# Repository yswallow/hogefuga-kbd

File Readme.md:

### hogefuga keyboard

#### PCB size

```
Plate:  76.2mm x 95.25mm, 1.2mm thick
PCB:    97.7mm x 95.25mm
bottom: 97.7mm x 95.25mm
```

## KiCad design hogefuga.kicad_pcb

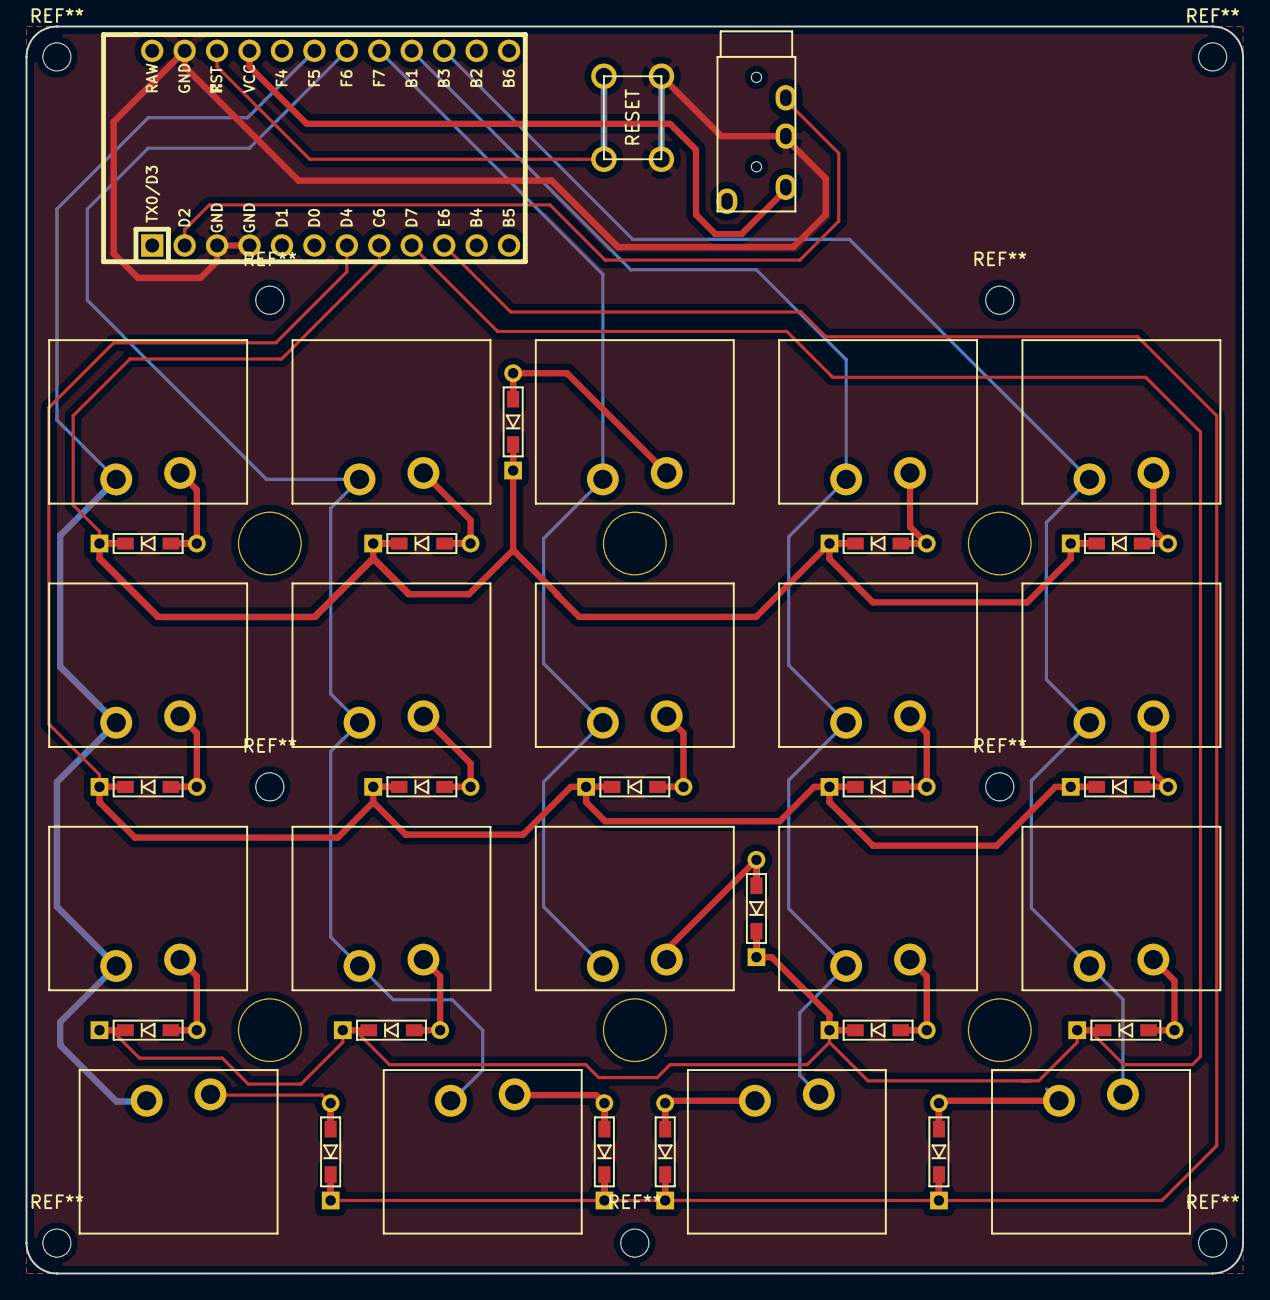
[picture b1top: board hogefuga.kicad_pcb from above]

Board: 2 copper layers, 95.3 x 97.6 mm, 47 parts (0 on the bottom side), 32 nets.

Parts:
D1, D2, D3, D4, D5, D6, D7, D8, D9, D10, D11, D12, D13, D14, D15, D16, D17, D18, D19: D; D3_TH_SMD
J1: MJ-4PP-9; Keebio-PJ-320A
Ref**: Val**; HOLE
Ref**#2, Ref**#3, Ref**#4, Ref**#5, Ref**#6: Val**; HOLE
SW1, SW2, SW3, SW4, SW5, SW6, SW7, SW8, SW9, SW10, SW11, SW12, SW13, SW14, SW15, SW16, SW17, SW18, SW19: SW_PUSH; ALPS_SKCM
SW20: SW_PUSH; ResetSW_4P
U1: ProMicro; ArduinoProMicro

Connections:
GND: J1.C, SW20.2, U1.3, U1.4, U1.23
unnamed: D1.2, SW1.1
unnamed: D2.2, SW2.1
unnamed: D3.2, SW3.1
unnamed: D4.2, SW4.1
unnamed: D5.2, SW5.1
unnamed: D6.2, SW6.1
unnamed: D7.2, SW7.1
unnamed: D8.2, SW8.1
unnamed: D9.2, SW9.1
unnamed: D10.2, SW10.1
unnamed: D11.2, SW11.1
unnamed: D12.2, SW12.1
unnamed: D13.2, SW13.1
unnamed: D14.2, SW14.1
unnamed: D15.2, SW15.1
unnamed: D16.2, SW16.2
unnamed: D17.2, SW17.2
unnamed: D18.2, SW18.1
unnamed: D19.2, SW19.1
VCC: J1.D, U1.21
col1: SW1.2, SW6.2, SW11.2, SW16.1, U1.19
col2: SW2.2, SW7.2, SW12.2, SW17.1, U1.18
col3: SW3.2, SW8.2, SW13.2, U1.17
col4: SW4.2, SW9.2, SW14.2, SW18.2, U1.16
col5: SW5.2, SW10.2, SW15.2, SW19.2, U1.15
data: J1.B, U1.2
reset: SW20.1, U1.22
row0: D1.1, D2.1, D3.1, D4.1, D5.1, U1.8
row1: D6.1, D7.1, D8.1, D9.1, D10.1, U1.7
row2: D11.1, D12.1, D13.1, D14.1, D15.1, U1.9
row3: D16.1, D17.1, D18.1, D19.1, U1.10

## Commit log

2018-10-12 init
2018-10-12 jack moved
2018-10-12 GND塗りつぶし
2018-10-12 bold GND, without 塗りつぶし
2018-10-12 add credit
2018-10-12 pre release
2018-10-12 add Readme
2018-10-13 rev0.2
2018-10-13 PCBを直接ボトムプレートに固定する穴を追加
2018-10-14 寸法を追加
2018-10-14 add KLE info
2018-10-14 ignore autosave file
2018-10-15 move TRRS jack
2018-10-15 配線の軽微な変更
2018-10-16 スイッチを全てtmkさんのフットプリントに変更
2018-10-16 ボトムプレートの片面を導体で塗りつぶす試み
2018-10-16 プレートからボトムへのネジを追加
